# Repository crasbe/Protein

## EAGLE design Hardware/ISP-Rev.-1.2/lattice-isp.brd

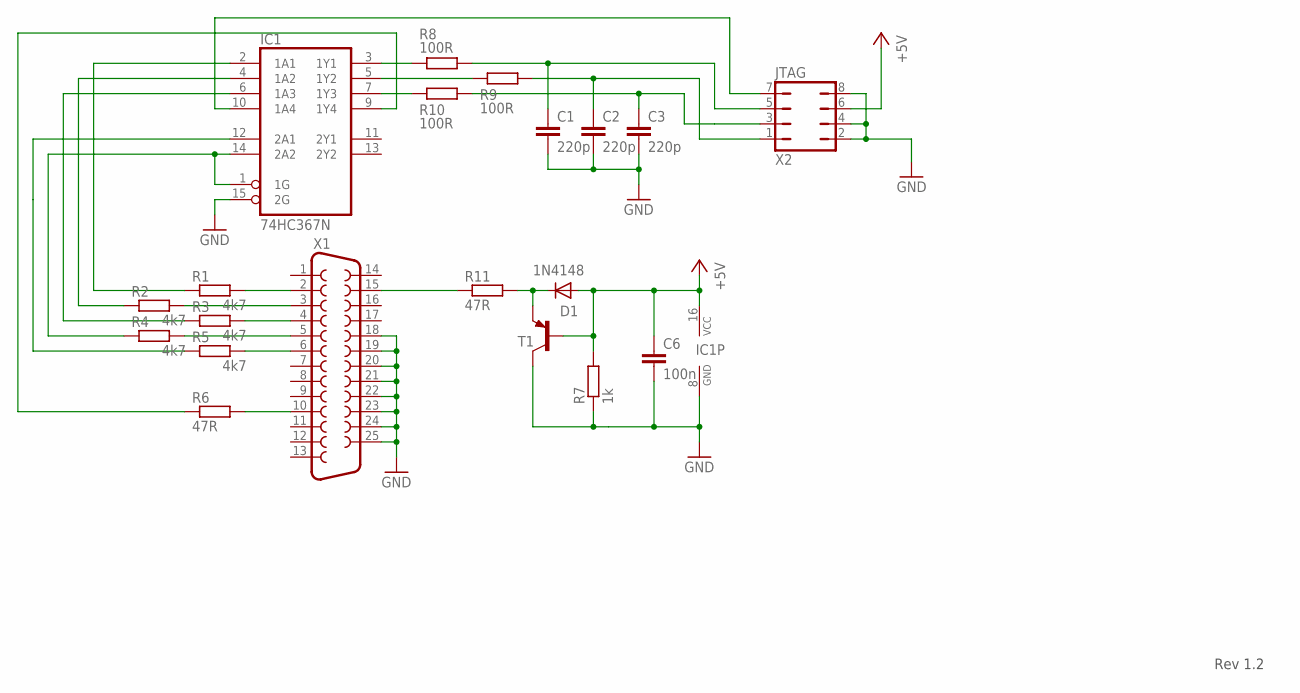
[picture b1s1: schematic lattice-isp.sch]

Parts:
C1, C2, C3: 220p; C025-024X044
C6: 100n; C050-024X044
D1: 1N4148; DO35-7
IC1: 74HC367N; DIL16
R1, R2, R3, R4, R5: 4k7; 0207/10
R6, R11: 47R; 0207/10
R7: 1k; 0207/10
R8, R9, R10: 100R; 0207/10
T1: BC636-PNP-TO92-BCE; TO92-BCE
X1: F25HP
X2: JTAG; JP4Q

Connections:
+5V: C6.1, D1.A, IC1.16 (VCC), R7.2, T1.B, X2.6
GND: C1.2, C2.2, C3.2, C6.2, IC1.8 (GND), IC1.15 (2G), R7.1, T1.C, X1.18, X1.19, X1.20, X1.21, X1.22, X1.23, X1.24, X1.25, X2.2, X2.4, X2.8
unnamed: IC1.3 (1Y1), R8.1
unnamed: R1.2, X1.2
unnamed: R2.2, X1.3
unnamed: R3.2, X1.4
unnamed: R4.2, X1.5
unnamed: R5.2, X1.6
unnamed: R6.2, X1.10
unnamed: IC1.2 (1A1), R1.1
unnamed: IC1.4 (1A2), R2.1
unnamed: IC1.6 (1A3), R3.1
unnamed: IC1.1 (1G), IC1.14 (2A2), R4.1
unnamed: IC1.12 (2A1), R5.1
unnamed: IC1.9 (1Y4), R6.1
unnamed: IC1.5 (1Y2), R9.1
unnamed: IC1.7 (1Y3), R10.1
unnamed: C3.1, R10.2, X2.3
unnamed: D1.C, R11.2, T1.E
unnamed: R11.1, X1.15
TCK: C2.1, R9.2, X2.1
TDI: C1.1, R8.2, X2.5
TDO: IC1.10 (1A4), X2.7

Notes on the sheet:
Rev 1.2

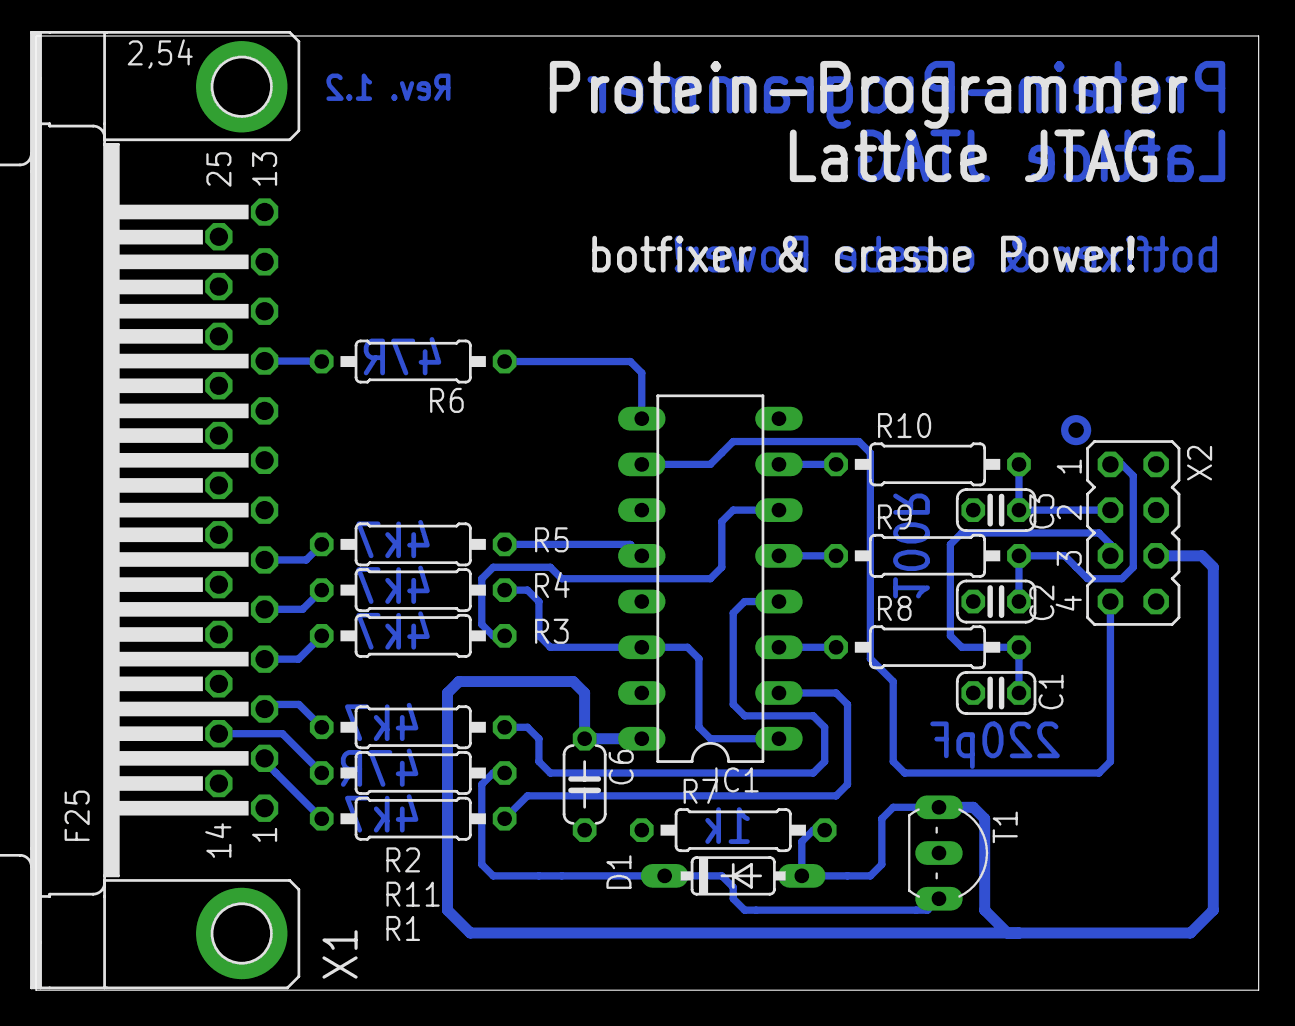
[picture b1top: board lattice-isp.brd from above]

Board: 2 copper layers, 67.9 x 53.0 mm, 20 parts (0 on the bottom side), 23 nets.

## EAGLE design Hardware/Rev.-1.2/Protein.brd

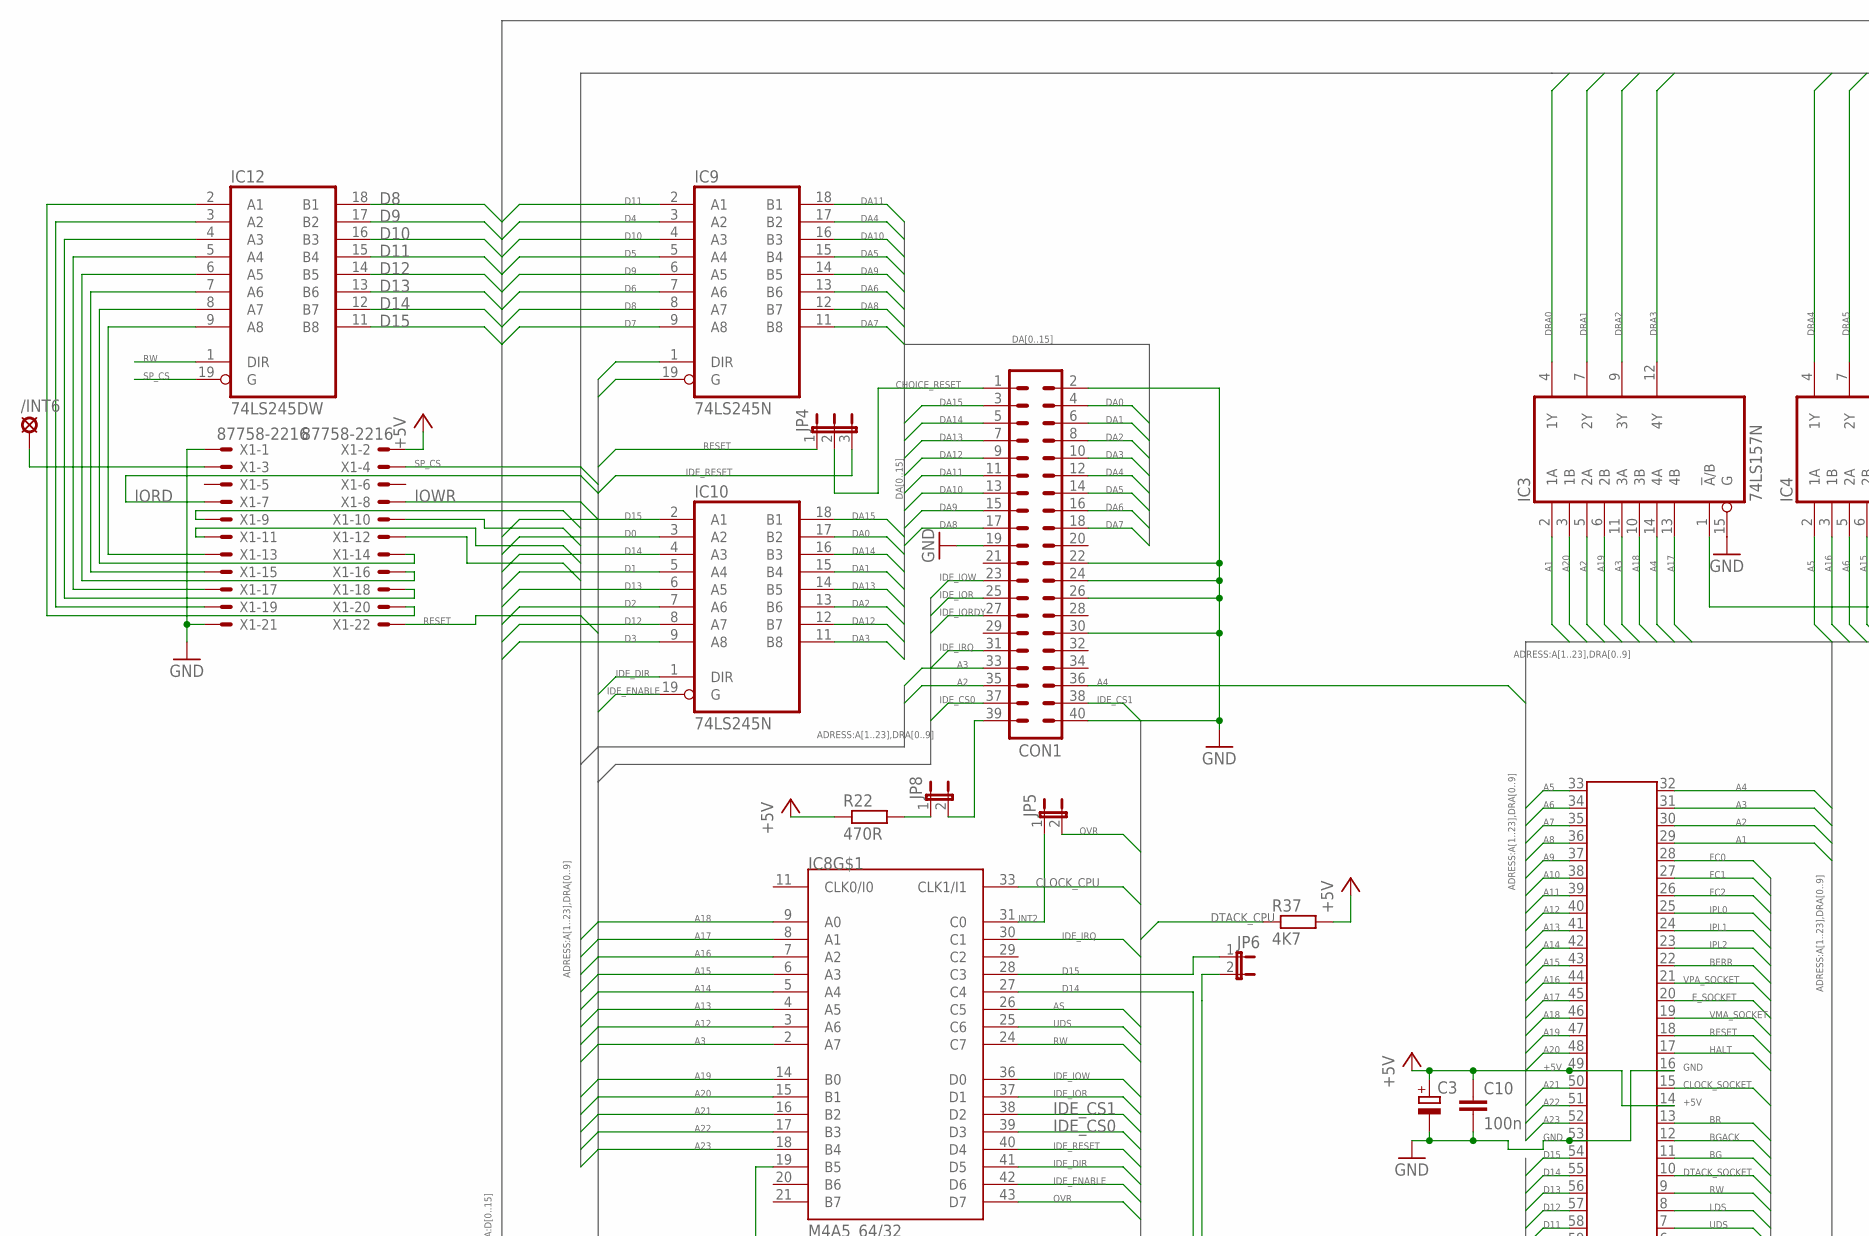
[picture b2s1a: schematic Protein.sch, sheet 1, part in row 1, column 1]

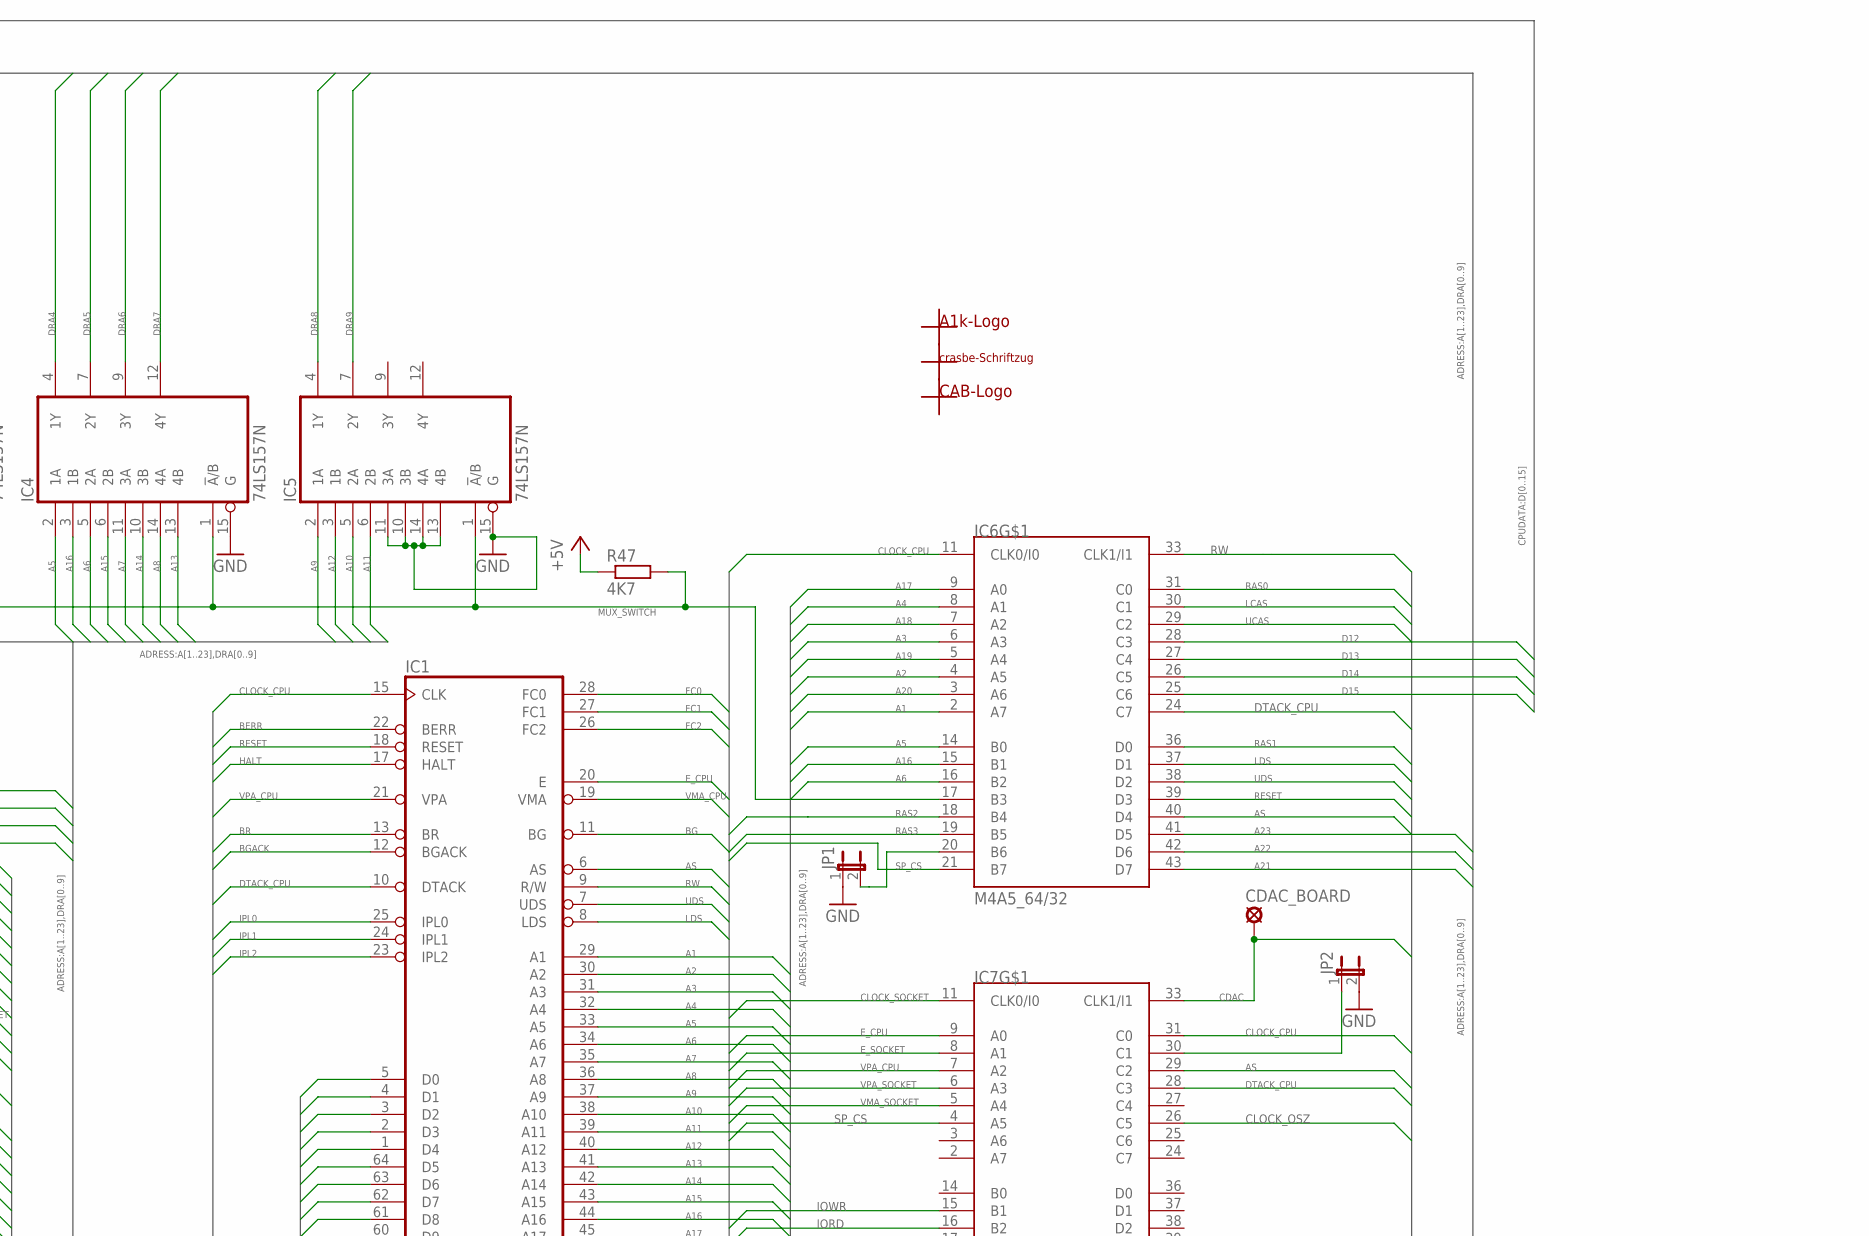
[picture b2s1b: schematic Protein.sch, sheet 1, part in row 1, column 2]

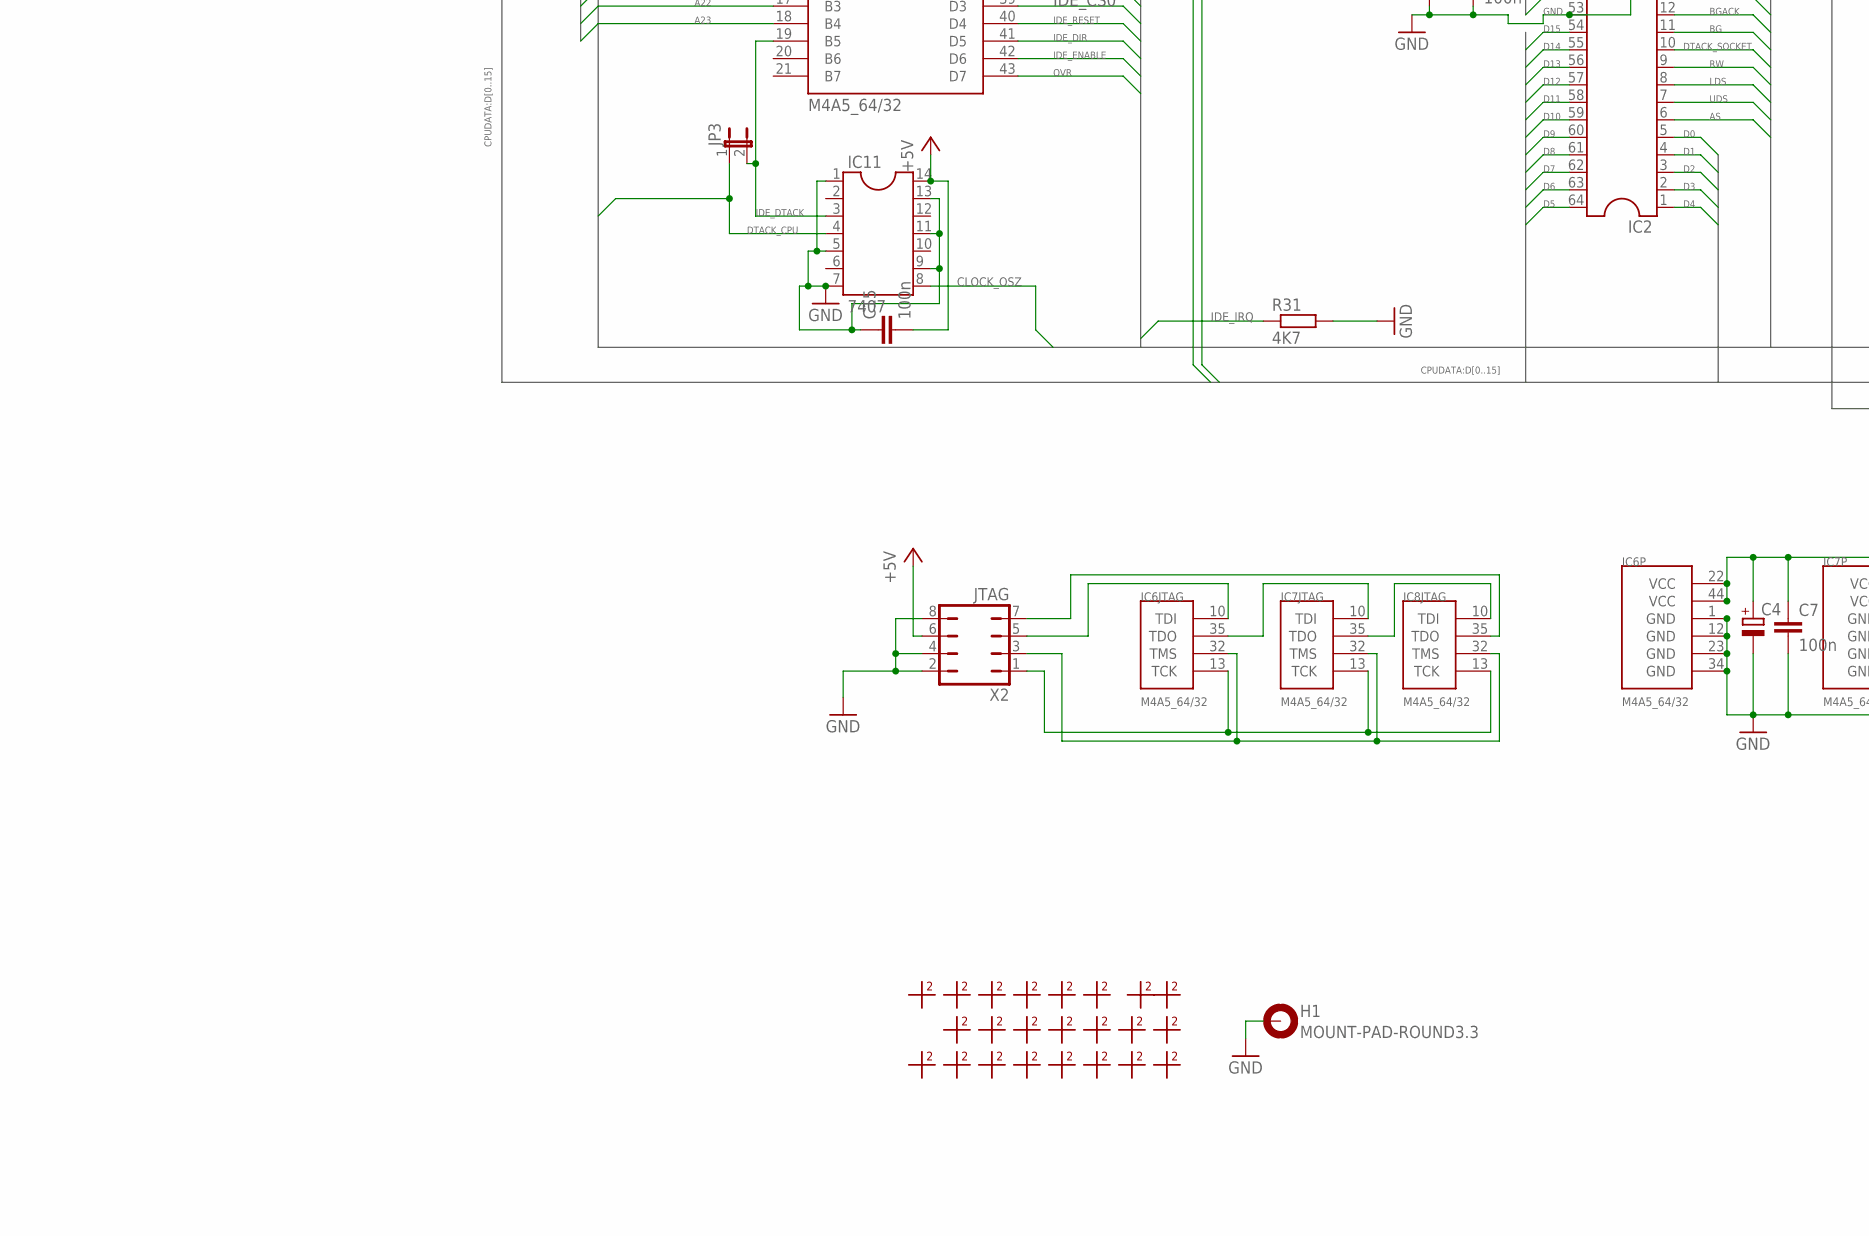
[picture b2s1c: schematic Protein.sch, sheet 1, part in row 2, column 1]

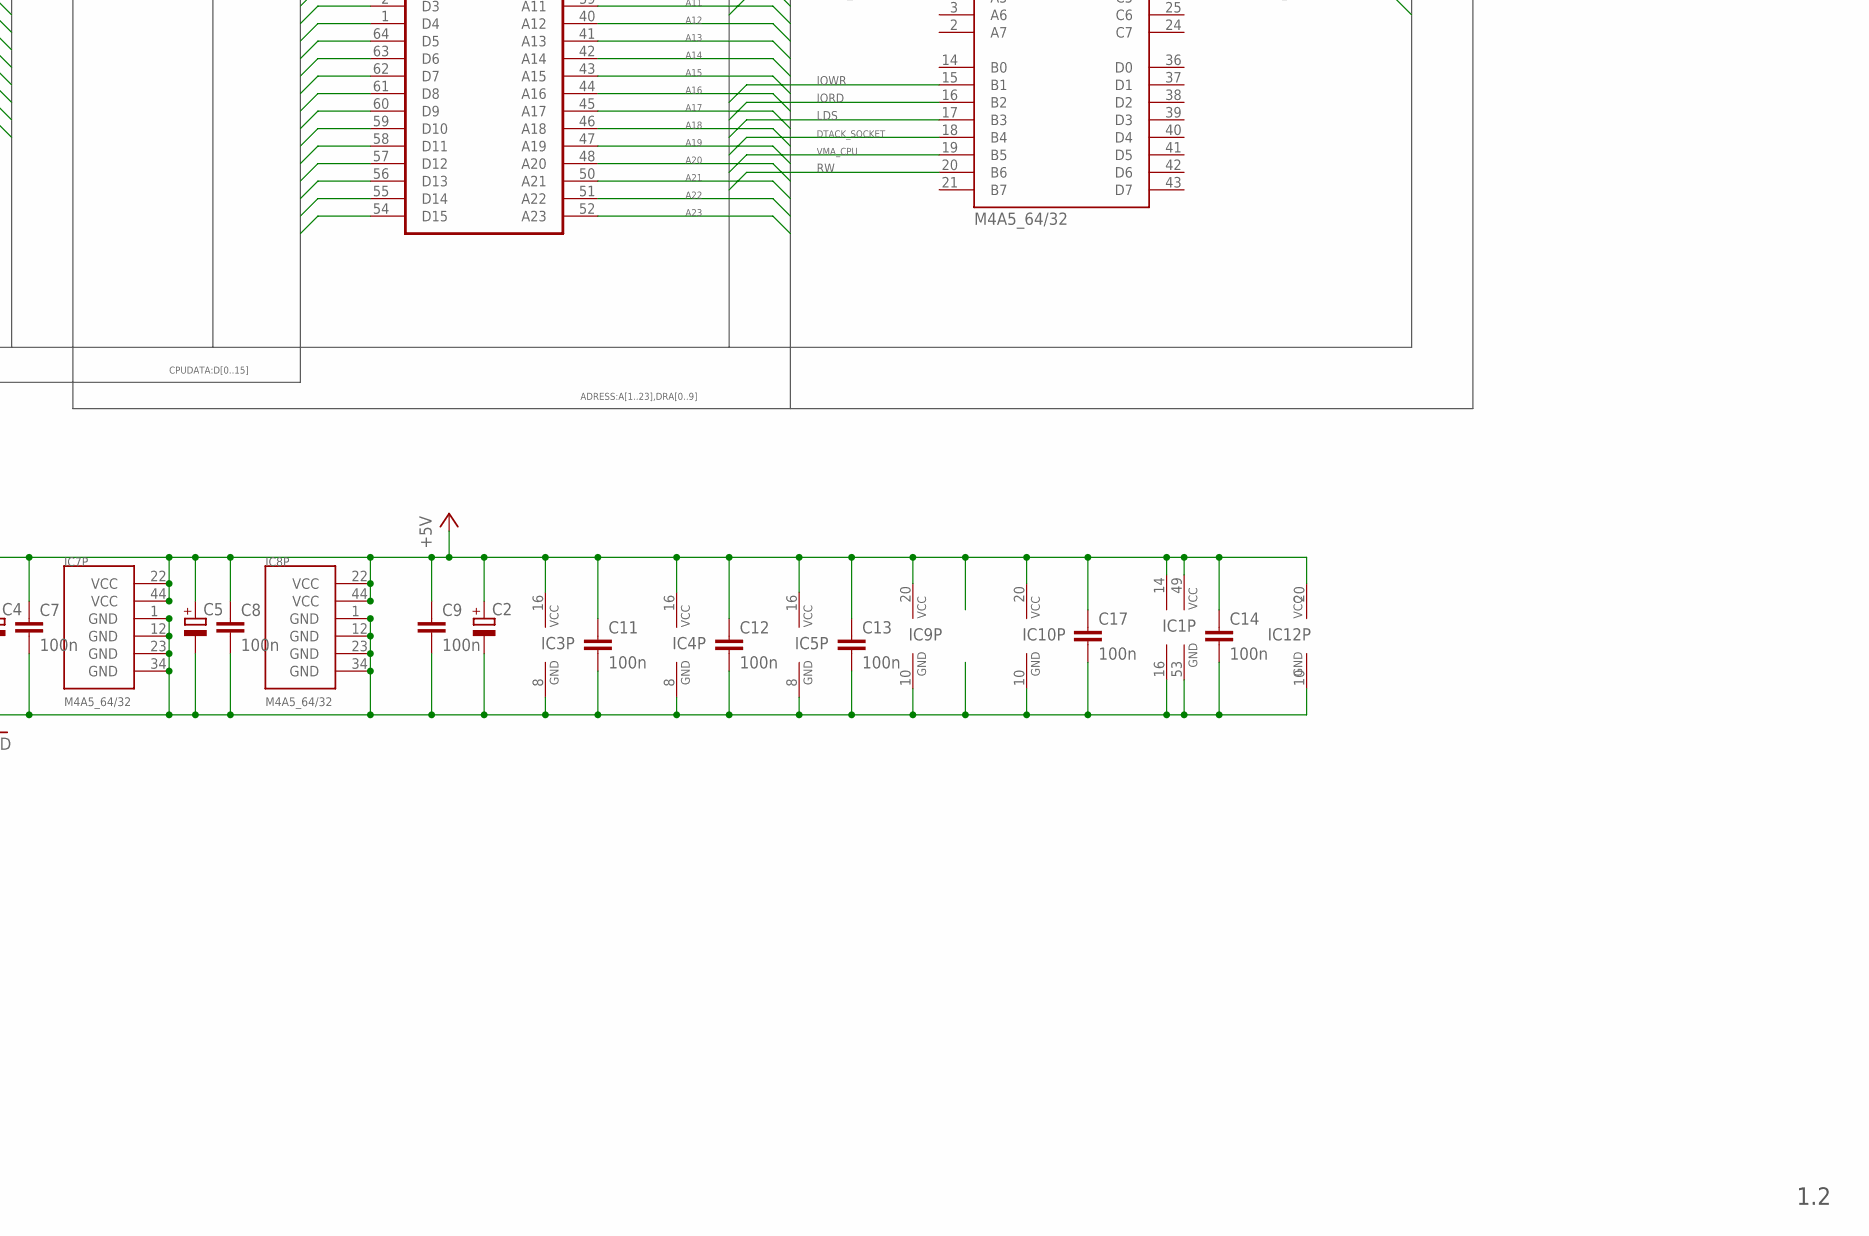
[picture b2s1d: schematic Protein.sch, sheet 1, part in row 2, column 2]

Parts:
/INT6: SE11
C2, C3, C4, C5: CPOL-EUE2.5-7; E2,5-7
C7, C8, C9, C10, C11, C12, C13, C15, C17: 100n; C025-024X044
C14: 100n; C1206K
CDAC_BOARD: SE11
CON1: ML40
H1: MOUNT-PAD-ROUND3.3; 3,3-PAD
IC1: MC68000P; DIL64
IC2: DIL64
IC3, IC4, IC5: 74LS157N; DIL16
IC6, IC7, IC8: M4A5_64/32; PLCC-S44
IC9, IC10: 74LS245N; DIL20
IC11: 7407; DIL14
IC12: 74LS245DW; SO20W
JP1, JP2, JP3, JP5, JP6, JP8: JP1E; JP1
JP4: JP2E; JP2
R22: 470R; 0207/10
R31, R37, R47: 4K7; M0805
U$1: A1K
U$2: CRASBE
U$3: CAB; CAB-LOGO
U$5, U$8, U$9, U$10, U$11, U$13, U$14, U$15, U$16, U$17, U$18, U$19, U$20, U$21, U$22, U$23, U$24, U$25, U$26, U$27, U$28, U$29, U$30: BREAD_2; BREAD
X1: 87758-2216
X2: JTAG; JP4Q

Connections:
+5V: C2.+, C3.+, C4.+, C5.+, C7.1, C8.1, C9.1, C10.1, C11.1, C12.1, C13.1, C14.1, C15.2, C17.1, IC1.14 (VCC), IC1.49 (VCC), IC2.14, IC2.49, IC3.16 (VCC), IC4.16 (VCC), IC5.16 (VCC), IC6.22 (VCC), IC6.44 (VCC), IC7.22 (VCC), IC7.44 (VCC), IC8.22 (VCC), IC8.44 (VCC), IC9.20 (VCC), IC10.20 (VCC), IC11.14, IC12.20 (VCC), R22.1, R37.2, R47.1, X1.2, X2.6; also elsewhere on the board
A1: IC1.29 (A1), IC2.29, IC3.2 (1A), IC6.2 (A7)
A2: CON1.35, IC1.30 (A2), IC2.30, IC3.5 (2A), IC6.4 (A5), X1.12
A3: CON1.33, IC1.31 (A3), IC2.31, IC3.11 (3A), IC6.6 (A3), IC8.2 (A7), X1.11
A4: CON1.36, IC1.32 (A4), IC2.32, IC3.14 (4A), IC6.8 (A1), X1.10
A5: IC1.33 (A5), IC2.33, IC4.2 (1A), IC6.14 (B0), X1.9
A6: IC1.34 (A6), IC2.34, IC4.5 (2A), IC6.16 (B2)
A7: IC1.35 (A7), IC2.35, IC4.11 (3A)
A8: IC1.36 (A8), IC2.36, IC4.14 (4A)
A9: IC1.37 (A9), IC2.37, IC5.2 (1A)
A10: IC1.38 (A10), IC2.38, IC5.5 (2A)
A11: IC1.39 (A11), IC2.39, IC5.6 (2B)
A12: IC1.40 (A12), IC2.40, IC5.3 (1B), IC8.3 (A6)
A13: IC1.41 (A13), IC2.41, IC4.13 (4B), IC8.4 (A5)
A14: IC1.42 (A14), IC2.42, IC4.10 (3B), IC8.5 (A4)
A15: IC1.43 (A15), IC2.43, IC4.6 (2B), IC8.6 (A3)
A16: IC1.44 (A16), IC2.44, IC4.3 (1B), IC6.15 (B1), IC8.7 (A2)
A17: IC1.45 (A17), IC2.45, IC3.13 (4B), IC6.9 (A0), IC8.8 (A1)
A18: IC1.46 (A18), IC2.46, IC3.10 (3B), IC6.7 (A2), IC8.9 (A0)
A19: IC1.47 (A19), IC2.47, IC3.6 (2B), IC6.5 (A4), IC8.14 (B0)
A20: IC1.48 (A20), IC2.48, IC3.3 (1B), IC6.3 (A6), IC8.15 (B1)
A21: IC1.50 (A21), IC2.50, IC6.43 (D7), IC8.16 (B2)
A22: IC1.51 (A22), IC2.51, IC6.42 (D6), IC8.17 (B3)
A23: IC1.52 (A23), IC2.52, IC6.41 (D5), IC8.18 (B4)
AS: IC1.6 (AS), IC2.6, IC6.40 (D4), IC7.29 (C2), IC8.26 (C5)
BERR: IC1.22 (BERR), IC2.22
BG: IC1.11 (BG), IC2.11
BGACK: IC1.12 (BGACK), IC2.12
BR: IC1.13 (BR), IC2.13
CDAC: CDAC_BOARD.MP, IC7.33 (CLK1/I1)
CHOICE_RESET: CON1.1, JP4.2
CLOCK_CPU: IC1.15 (CLK), IC6.11 (CLK0/I0), IC7.31 (C0), IC8.33 (CLK1/I1)
CLOCK_OSZ: IC7.26 (C5), IC11.8
CLOCK_SOCKET: IC2.15, IC7.11 (CLK0/I0)
D0: IC1.5 (D0), IC2.5, IC10.3 (A2); also elsewhere on the board
D1: IC1.4 (D1), IC2.4, IC10.5 (A4); also elsewhere on the board
D2: IC1.3 (D2), IC2.3, IC10.7 (A6); also elsewhere on the board
D3: IC1.2 (D3), IC2.2, IC10.9 (A8); also elsewhere on the board
D4: IC1.1 (D4), IC2.1, IC9.3 (A2); also elsewhere on the board
D5: IC1.64 (D5), IC2.64, IC9.5 (A4); also elsewhere on the board
D6: IC1.63 (D6), IC2.63, IC9.7 (A6); also elsewhere on the board
D7: IC1.62 (D7), IC2.62, IC9.9 (A8); also elsewhere on the board
D8: IC1.61 (D8), IC2.61, IC9.8 (A7), IC12.18 (B1); also elsewhere on the board
D9: IC1.60 (D9), IC2.60, IC9.6 (A5), IC12.17 (B2); also elsewhere on the board
D10: IC1.59 (D10), IC2.59, IC9.4 (A3), IC12.16 (B3); also elsewhere on the board
D11: IC1.58 (D11), IC2.58, IC9.2 (A1), IC12.15 (B4); also elsewhere on the board
D12: IC1.57 (D12), IC2.57, IC6.28 (C3), IC10.8 (A7), IC12.14 (B5); also elsewhere on the board
D13: IC1.56 (D13), IC2.56, IC6.27 (C4), IC10.6 (A5), IC12.13 (B6); also elsewhere on the board
D14: IC1.55 (D14), IC2.55, IC6.26 (C5), IC8.27 (C4), IC10.4 (A3), IC12.12 (B7); also elsewhere on the board
D15: IC1.54 (D15), IC2.54, IC6.25 (C6), IC10.2 (A1), IC12.11 (B8), JP6.2; also elsewhere on the board
DA0: CON1.4, IC10.17 (B2)
DA1: CON1.6, IC10.15 (B4)
DA2: CON1.8, IC10.13 (B6)
DA3: CON1.10, IC10.11 (B8)
DA4: CON1.12, IC9.17 (B2)
DA5: CON1.14, IC9.15 (B4)
DA6: CON1.16, IC9.13 (B6)
DA7: CON1.18, IC9.11 (B8)
DA8: CON1.17, IC9.12 (B7)
DA9: CON1.15, IC9.14 (B5)
DA10: CON1.13, IC9.16 (B3)
DA11: CON1.11, IC9.18 (B1)
DA12: CON1.9, IC10.12 (B7)
DA13: CON1.7, IC10.14 (B5)
DA14: CON1.5, IC10.16 (B3)
DA15: CON1.3, IC10.18 (B1)
DRA0: IC3.4 (1Y); also elsewhere on the board
DRA1: IC3.7 (2Y); also elsewhere on the board
DRA2: IC3.9 (3Y); also elsewhere on the board
DRA3: IC3.12 (4Y); also elsewhere on the board
DRA4: IC4.4 (1Y); also elsewhere on the board
DRA5: IC4.7 (2Y); also elsewhere on the board
DRA6: IC4.9 (3Y); also elsewhere on the board
DRA7: IC4.12 (4Y); also elsewhere on the board
DRA8: IC5.4 (1Y); also elsewhere on the board
DRA9: IC5.7 (2Y); also elsewhere on the board
DTACK_CPU: IC1.10 (DTACK), IC6.24 (C7), IC7.28 (C3), IC11.4, JP3.1, R37.1
DTACK_SOCKET: IC2.10, IC7.18 (B4)
E_CPU: IC1.20 (E), IC7.9 (A0)
E_SOCKET: IC2.20, IC7.8 (A1)
FC0: IC1.28 (FC0), IC2.28
FC1: IC1.27 (FC1), IC2.27
FC2: IC1.26 (FC2), IC2.26
GND: C2.-, C3.-, C4.-, C5.-, C7.2, C8.2, C9.2, C10.2, C11.2, C12.2, C13.2, C14.2, C15.1, C17.2, CON1.2, CON1.19, CON1.22, CON1.24, CON1.26, CON1.30, CON1.40, H1.B3,3, IC1.16 (GND), IC1.53 (GND), IC2.16, IC2.53, IC3.8 (GND), IC3.15 (G), IC4.8 (GND), IC4.15 (G), IC5.8 (GND), IC5.10 (3B), IC5.11 (3A), IC5.13 (4B), IC5.14 (4A), IC5.15 (G), IC6.1 (GND), IC6.12 (GND), IC6.23 (GND), IC6.34 (GND), IC7.1 (GND), IC7.12 (GND), IC7.23 (GND), IC7.34 (GND), IC8.1 (GND), IC8.12 (GND), IC8.23 (GND), IC8.34 (GND), IC9.10 (GND), IC10.10 (GND), IC11.1, IC11.5, IC11.7, IC11.9, IC11.11, IC11.13, IC12.10 (GND), JP1.1, JP2.2, R31.2, X1.1, X1.21, X2.2, X2.4, X2.8; also elsewhere on the board
HALT: IC1.17 (HALT), IC2.17
IDE_CS0: CON1.37, IC8.39 (D3)
IDE_CS1: CON1.38, IC8.38 (D2)
IDE_DIR: IC8.41 (D5), IC9.1 (DIR), IC10.1 (DIR)
IDE_DTACK: IC8.19 (B5), IC11.3, JP3.2
IDE_ENABLE: IC8.42 (D6), IC9.19 (G), IC10.19 (G)
IDE_IOR: CON1.25, IC8.37 (D1)
IDE_IORDY: CON1.27
IDE_IOW: CON1.23, IC8.36 (D0)
IDE_IRQ: CON1.31, IC8.30 (C1), R31.1
IDE_RESET: IC8.40 (D4), JP4.3
INT2: IC8.31 (C0), JP5.1
IORD: IC7.16 (B2), X1.7
IOWR: IC7.15 (B1), X1.8
IPL0: IC1.25 (IPL0), IC2.25
IPL1: IC1.24 (IPL1), IC2.24
IPL2: IC1.23 (IPL2), IC2.23
LCAS: IC6.30 (C1); also elsewhere on the board
LDS: IC1.8 (LDS), IC2.8, IC6.37 (D1), IC7.17 (B3)
MUX_SWITCH: IC3.1 (!A!/B), IC4.1 (!A!/B), IC5.1 (!A!/B), IC6.17 (B3), R47.2
unnamed: IC6.20 (B6), JP1.2
unnamed: IC8.28 (C3), JP6.1
unnamed: IC7.30 (C1), JP2.1
unnamed: JP8.1, R22.2
unnamed: CON1.39, JP8.2
unnamed: IC6.35 (TDO), IC7.10 (TDI)
unnamed: IC7.35 (TDO), IC8.10 (TDI)
unnamed: /INT6.MP, X1.3
unnamed: IC12.8 (A7), X1.14
unnamed: IC12.9 (A8), X1.13
unnamed: IC12.7 (A6), X1.15
unnamed: IC12.6 (A5), X1.16
unnamed: IC12.5 (A4), X1.17
unnamed: IC12.4 (A3), X1.18
unnamed: IC12.3 (A2), X1.19
unnamed: IC12.2 (A1), X1.20
OVR: IC8.43 (D7), JP5.2
RAS0: IC6.31 (C0); also elsewhere on the board
RAS1: IC6.36 (D0); also elsewhere on the board
RAS2: IC6.18 (B4); also elsewhere on the board
RAS3: IC6.19 (B5); also elsewhere on the board
RESET: IC1.18 (RESET), IC2.18, IC6.39 (D3), JP4.1, X1.22
RW: IC1.9 (R/W), IC2.9, IC6.33 (CLK1/I1), IC7.20 (B6), IC8.24 (C7), IC12.1 (DIR); also elsewhere on the board
SP_CS: IC6.21 (B7), IC7.4 (A5), IC12.19 (G), X1.4
TCK: IC6.13 (TCK), IC7.13 (TCK), IC8.13 (TCK), X2.1
TDI: IC8.35 (TDO), X2.7
TDO: IC6.10 (TDI), X2.5
TMS: IC6.32 (TMS), IC7.32 (TMS), IC8.32 (TMS), X2.3
UCAS: IC6.29 (C2); also elsewhere on the board
UDS: IC1.7 (UDS), IC2.7, IC6.38 (D2), IC8.25 (C6)
VMA_CPU: IC1.19 (VMA), IC7.19 (B5)
VMA_SOCKET: IC2.19, IC7.5 (A4)
VPA_CPU: IC1.21 (VPA), IC7.7 (A2)
VPA_SOCKET: IC2.21, IC7.6 (A3)

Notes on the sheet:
1.2

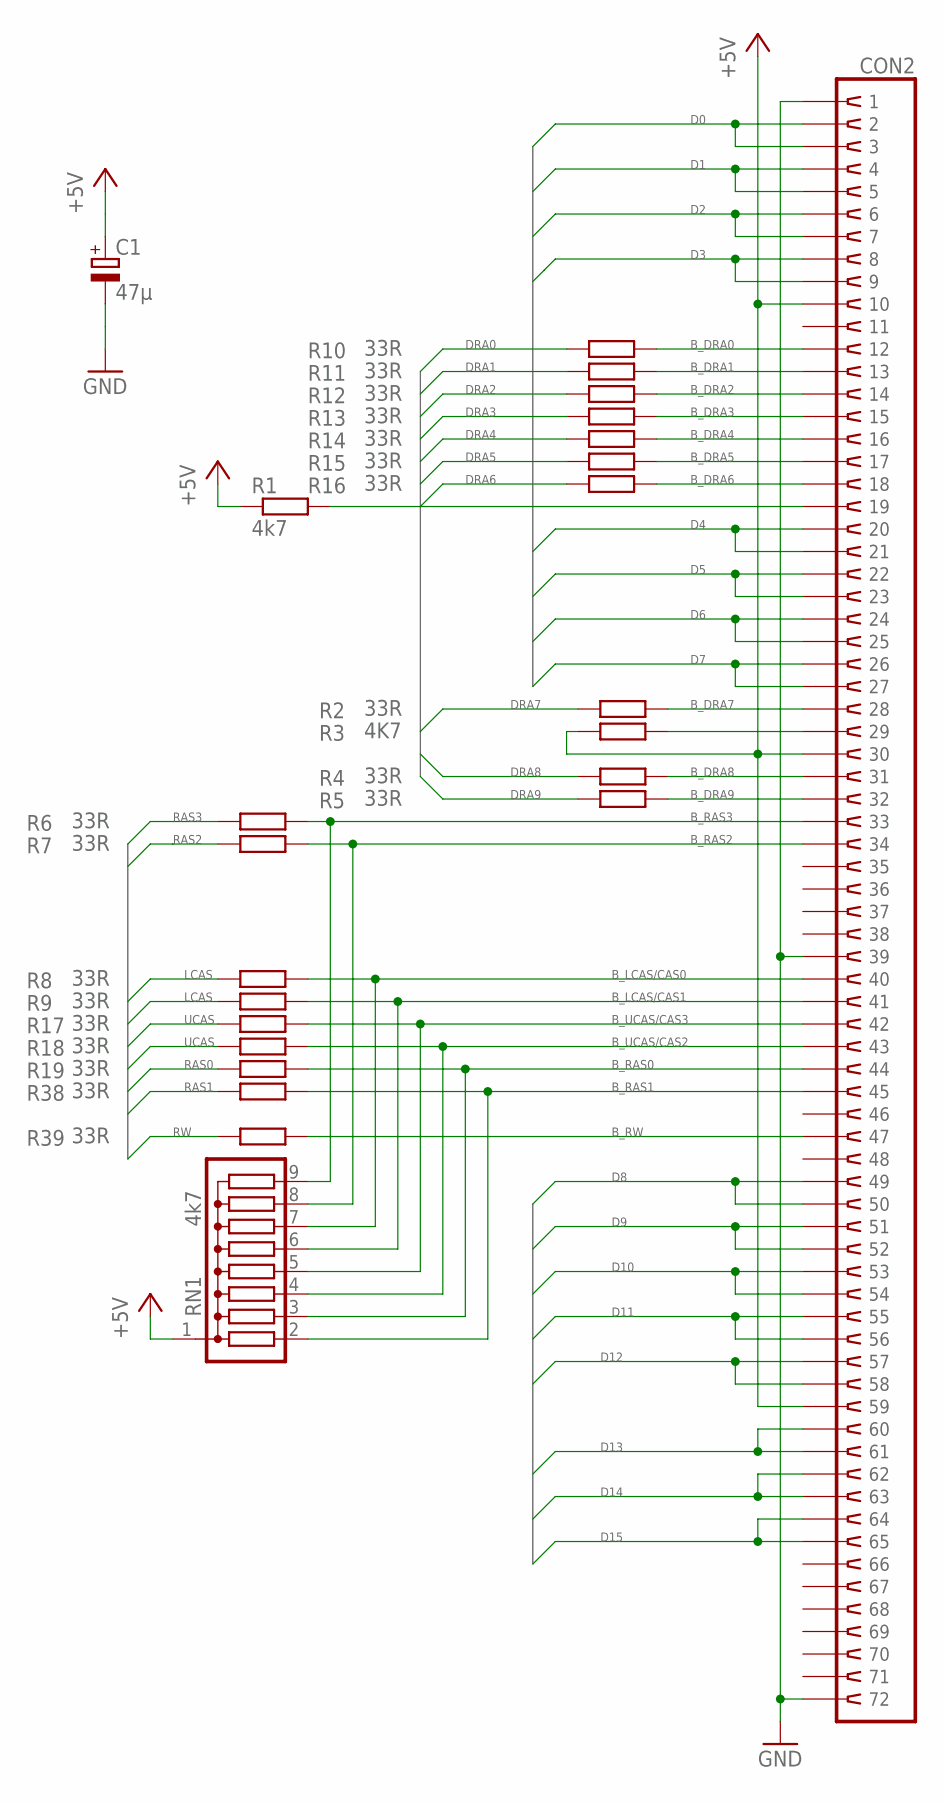
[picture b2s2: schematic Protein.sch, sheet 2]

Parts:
C1: 47µ; E1,8-4
CON2: SIMM72; 73826962
R1: 4k7; M0805
R2, R4, R5, R6, R7, R8, R9, R10, R11, R12, R13, R14, R15, R16, R17, R18, R19, R38, R39: 33R; 0207/10
R3: 4K7; 0207/10
RN1: 4k7; SIL9

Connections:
+5V: C1.+, CON2.10, CON2.30, CON2.59, R1.1, R3.1, RN1.1; also elsewhere on the board
B_DRA0: CON2.12, R10.2
B_DRA1: CON2.13, R11.2
B_DRA2: CON2.14, R12.2
B_DRA3: CON2.15, R13.2
B_DRA4: CON2.16, R14.2
B_DRA5: CON2.17, R15.2
B_DRA6: CON2.18, R16.2
B_DRA7: CON2.28, R2.2
B_DRA8: CON2.31, R4.2
B_DRA9: CON2.32, R5.2
B_LCAS/CAS0: CON2.40, R8.2, RN1.7
B_LCAS/CAS1: CON2.41, R9.2, RN1.6
B_RAS0: CON2.44, R19.2, RN1.3
B_RAS1: CON2.45, R38.2, RN1.2
B_RAS2: CON2.34, R7.2, RN1.8
B_RAS3: CON2.33, R6.2, RN1.9
B_RW: CON2.47, R39.2
B_UCAS/CAS2: CON2.43, R18.2, RN1.4
B_UCAS/CAS3: CON2.42, R17.2, RN1.5
D0: CON2.2, CON2.3; also elsewhere on the board
D1: CON2.4, CON2.5; also elsewhere on the board
D2: CON2.6, CON2.7; also elsewhere on the board
D3: CON2.8, CON2.9; also elsewhere on the board
D4: CON2.20, CON2.21; also elsewhere on the board
D5: CON2.22, CON2.23; also elsewhere on the board
D6: CON2.24, CON2.25; also elsewhere on the board
D7: CON2.26, CON2.27; also elsewhere on the board
D8: CON2.49, CON2.50; also elsewhere on the board
D9: CON2.51, CON2.52; also elsewhere on the board
D10: CON2.53, CON2.54; also elsewhere on the board
D11: CON2.55, CON2.56; also elsewhere on the board
D12: CON2.57, CON2.58; also elsewhere on the board
D13: CON2.60, CON2.61; also elsewhere on the board
D14: CON2.62, CON2.63; also elsewhere on the board
D15: CON2.64, CON2.65; also elsewhere on the board
DRA0: R10.1; also elsewhere on the board
DRA1: R11.1; also elsewhere on the board
DRA2: R12.1; also elsewhere on the board
DRA3: R13.1; also elsewhere on the board
DRA4: R14.1; also elsewhere on the board
DRA5: R15.1; also elsewhere on the board
DRA6: R16.1; also elsewhere on the board
DRA7: R2.1; also elsewhere on the board
DRA8: R4.1; also elsewhere on the board
DRA9: R5.1; also elsewhere on the board
GND: C1.-, CON2.1, CON2.39, CON2.72; also elsewhere on the board
LCAS: R8.1, R9.1; also elsewhere on the board
unnamed: CON2.19, R1.2
unnamed: CON2.29, R3.2
RAS0: R19.1; also elsewhere on the board
RAS1: R38.1; also elsewhere on the board
RAS2: R7.1; also elsewhere on the board
RAS3: R6.1; also elsewhere on the board
RW: R39.1; also elsewhere on the board
UCAS: R17.1, R18.1; also elsewhere on the board

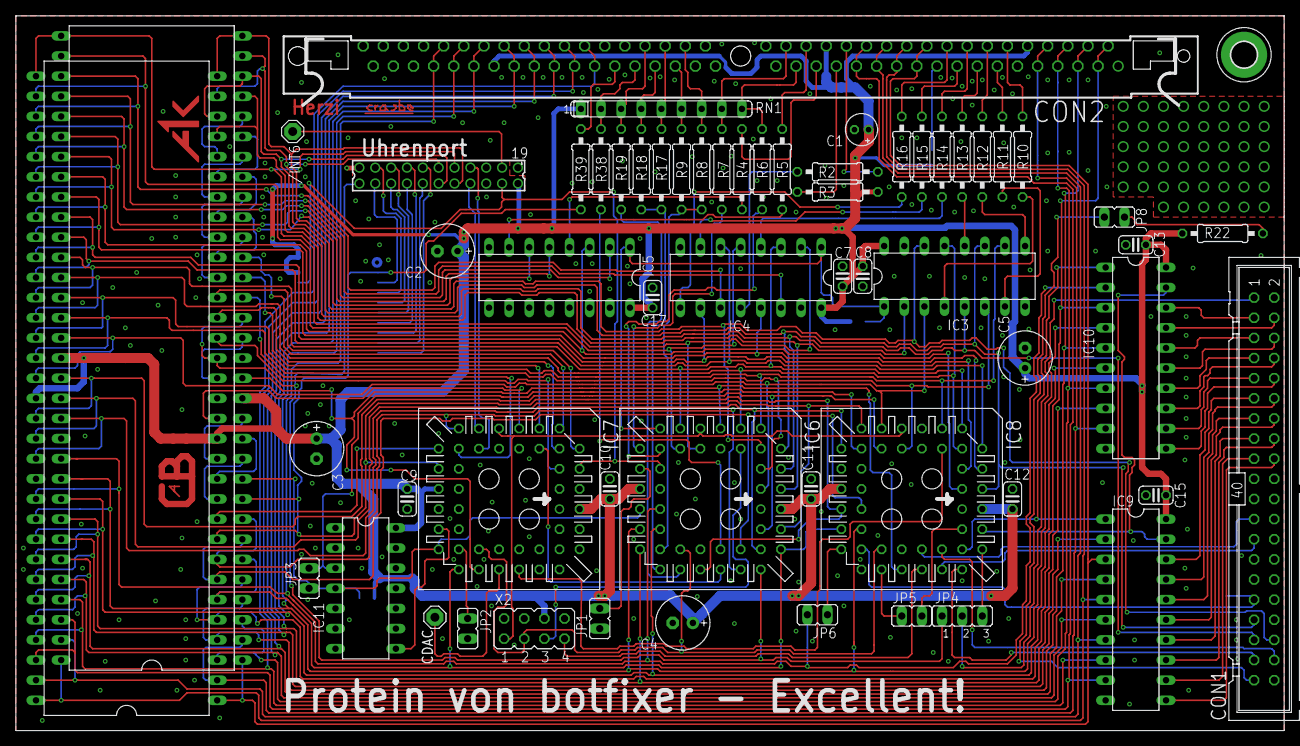
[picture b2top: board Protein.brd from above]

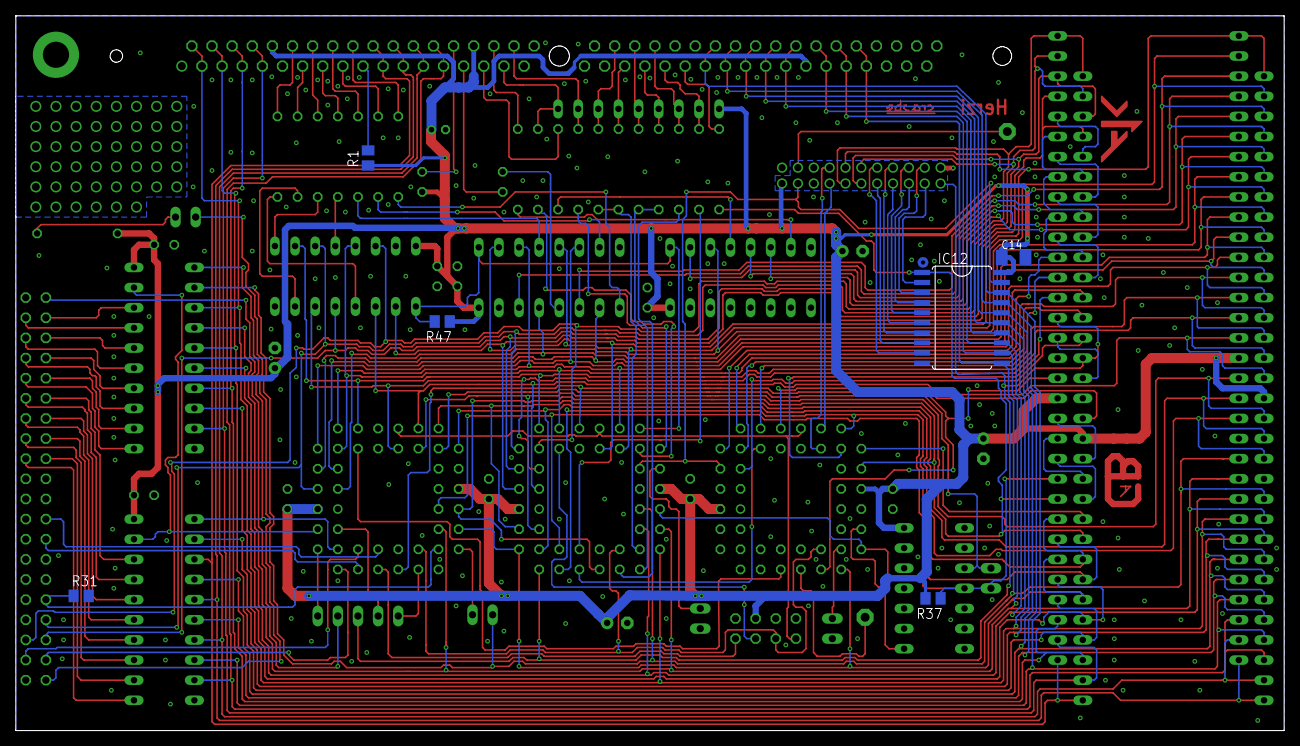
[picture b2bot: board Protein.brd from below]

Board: 2 copper layers, 160.0 x 90.2 mm, 93 parts (6 on the bottom side), 158 nets.

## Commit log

2015-08-30 generic pdfs and pngs added
2015-08-30 original protein sources added
2015-08-30 Some pictures added
